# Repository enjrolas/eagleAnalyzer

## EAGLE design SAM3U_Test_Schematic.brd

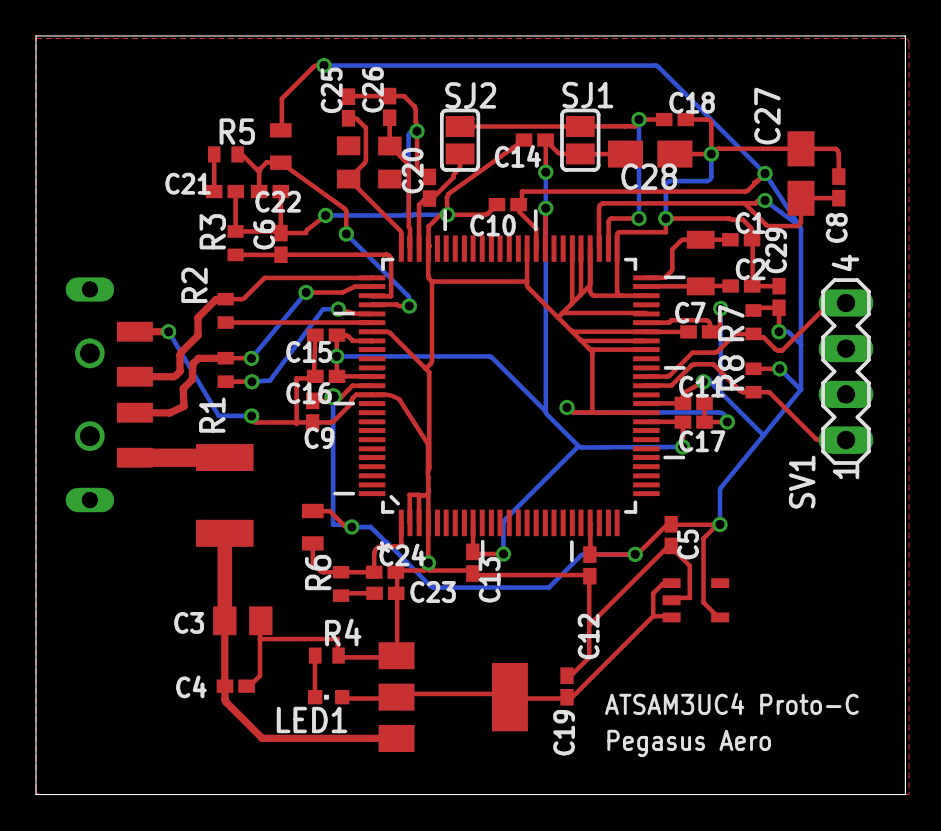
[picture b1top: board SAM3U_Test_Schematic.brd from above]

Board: 2 copper layers, 48.3 x 42.1 mm, 50 parts (0 on the bottom side), 24 nets.

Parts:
C1, C2, C25, C26: 20pF; C0402K
C3: 33uF; C0805K
C4, C7, C8, C9, C10, C11, C12, C13, C14, C15, C16, C17, C19, C20, C22, C24: 0.1uF; C0402K
C5: 10uF; C0402K
C6: 10pF; C0402K
C18, C21, C23: 4.7uF; C0402K
C27, C28: 10uF; A/3216-18R
C29: 10nF; C0402K
L1, L2: TDK_MLZ2012_INDUCTOR; TDK_MLZ_INDUCTOR_2012PACK
LED1: CHIPLED_0603
R1, R2: 39R; R0402
R3: 6.8K 1%; R0402
R4: 220R; R0402
R5, R6: 1R; R0402
R7, R8: 4.7K; R0402
SJ1, SJ2: SJ
SV1: MA04-1
U$1: USB_TYPE_A_KEYSTN; USB_TYPE_PLUG_KSTN_PACK
U$2: ATSAM3UC4-PA; QFP50P1600X1600X160-100N
U$3: 32678_KYOCERA; 32678_KYOCERA_PACK
U$4: MF-MSMF050-2; MF-MSMF050-PACK
U$5: NCP1117-55V; NCP1117-5-SOT
U$6: LP2985-33DBVR5-PIN; LP2985-33DBVR-SO
U$7: AVX_12MHZ_CRYSTAL_CX3225GB; AVX_12MHZ_CX3225GB_PACK

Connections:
+3V3: C5.1, C7.1, C8.1, C9.1, C10.1, C11.1, C12.1, C27.+, C29.1, L1.1, L2.1, R7.1, R8.1, U$2.22, U$2.36, U$2.45, U$2.53, U$2.60, U$2.88, U$6.5
+5V: C19.1, LED1.A, U$5.2, U$5.4, U$6.1, U$6.3
DFSDM: R1.2, U$2.80
DHSDM: R1.1, U$1.2, U$2.77
DHSDP: R2.1, U$1.3, U$2.76
GND: C1.2, C2.2, C3.2, C4.2, C5.2, C6.2, C7.2, C8.2, C9.2, C10.2, C11.2, C12.2, C13.2, C14.2, C15.2, C16.2, C17.2, C18.2, C19.2, C20.2, C21.2, C22.2, C23.2, C24.2, C25.2, C26.2, C27.-, C28.-, C29.2, R3.2, R4.2, U$1.4, U$2.2, U$2.3, U$2.4, U$2.35, U$2.42, U$2.43, U$2.44, U$2.46, U$2.48, U$2.51, U$2.54, U$2.55, U$2.56, U$2.61, U$2.72, U$2.82, U$2.89, U$5.1, U$6.2
unnamed: C2.1, U$2.49, U$3.2
unnamed: C1.1, U$2.50, U$3.1
unnamed: C26.1, U$2.74, U$7.3
unnamed: R2.2, U$2.81
unnamed: C3.1, C4.1, U$4.2, U$5.3
unnamed: LED1.C, R4.1
unnamed: C21.1, R5.1
unnamed: C23.1, R6.1
unnamed: C25.1, U$2.75, U$7.1
SCL0: R7.2, SV1.4, U$2.39
SDA0: R8.2, SV1.1, U$2.38
VBG: C6.1, R3.1, U$2.78
VBUS: U$1.1, U$4.1
VDDANA: C24.1, L2.2, R6.2, U$2.1
VDDCORE: C13.1, C14.1, C15.1, C16.1, C17.1, C28.+, SJ1.2, U$2.9, U$2.34, U$2.59, U$2.83, U$2.87
VDDOUT: C18.1, SJ1.1, SJ2.1, U$2.52
VDDPLL: C20.1, SJ2.2, U$2.73
VDDUTMI: C22.1, L1.2, R5.2, U$2.79

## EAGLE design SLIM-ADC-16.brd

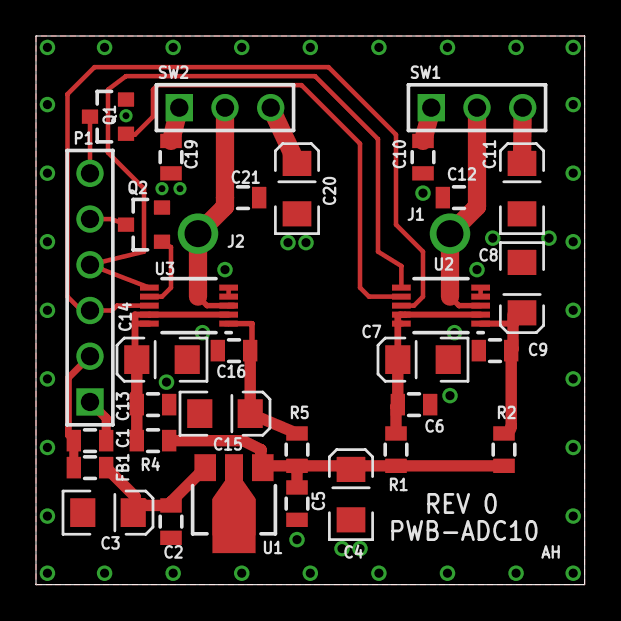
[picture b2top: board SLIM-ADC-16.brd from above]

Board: 2 copper layers, 30.5 x 30.5 mm, 34 parts (0 on the bottom side), 20 nets.

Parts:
C1, C2, C5, C6, C9, C10, C13, C16, C19: 0.1uF; 0805
C3, C4, C7, C8, C11, C14, C15, C20: 10uF/16V; EIA3216
C12, C21: 0.001uF; 0805
FB1: FERRITE0805; 0805
J1, J2: COAX; SLIM_COAX_PAD
P1: CONN-6PIN
Q1, Q2: MUN2211; SOT23
R1, R2, R4, R5: 10; 0805
SW1, SW2: SPDT-CONN; CONN-3PIN
U1: 78L05; SOT89
U2, U3: AD7685; MSOP10

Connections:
+5AD: C4.A, C5.1, R1.1, R2.2, R4.1, R5.2, U1.1
+10V: C1.1, FB1.1, P1.2
ACK: P1.5, Q2.C
CONVERT: P1.4, U2.6, U3.6
GND: C1.2, C2.2, C3.C, C4.C, C5.2, C6.2, C7.C, C8.C, C9.2, C10.2, C11.C, C12.2, C13.2, C14.C, C15.C, C16.2, C19.2, C20.C, C21.2, J1.P$2, J2.P$2, P1.1, Q1.E, Q2.E, U1.2, U1.4, U2.4, U2.5, U3.4, U3.5
unnamed: C8.A, C9.1, R2.1, U2.1
unnamed: C6.1, C7.A, R1.2, U2.2, U2.9, U2.10
unnamed: C12.1, J1.P$1, SW1.2, U2.3
unnamed: C10.1, SW1.1
unnamed: C11.A, SW1.3
unnamed: Q1.B, U2.7
unnamed: C2.1, C3.A, FB1.2, U1.3
unnamed: C15.A, C16.1, R5.1, U3.1
unnamed: C13.1, C14.A, R4.2, U3.2, U3.9, U3.10
unnamed: C21.1, J2.P$1, SW2.2, U3.3
unnamed: C19.1, SW2.1
unnamed: C20.A, SW2.3
unnamed: Q2.B, U3.7
SERCLOCK: P1.3, U2.8, U3.8
WAIT: P1.6, Q1.C

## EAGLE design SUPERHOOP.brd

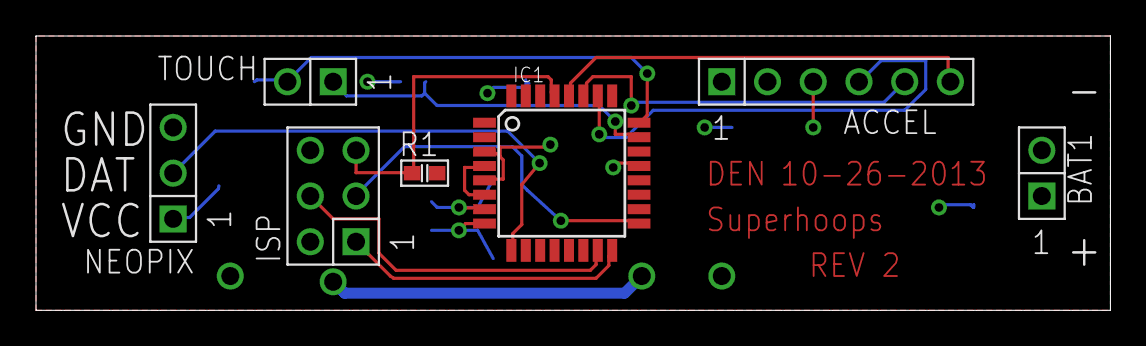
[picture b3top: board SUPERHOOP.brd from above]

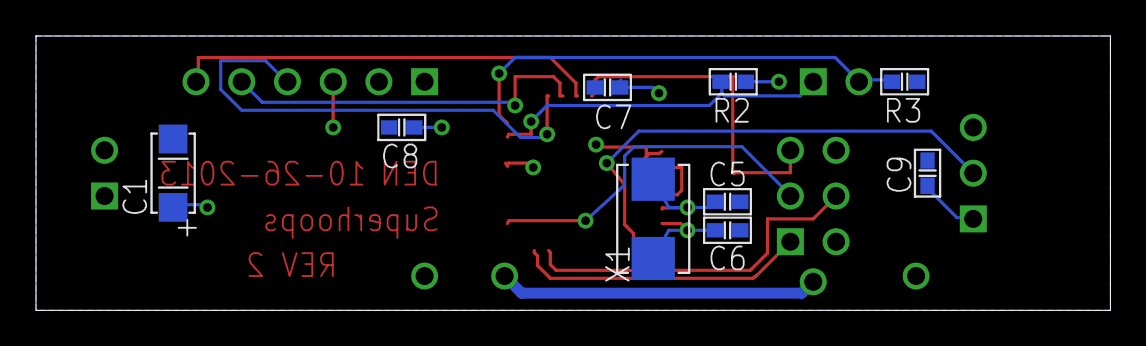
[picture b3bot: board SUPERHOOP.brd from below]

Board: 2 copper layers, 59.7 x 15.2 mm, 16 parts (9 on the bottom side), 14 nets.

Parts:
ACCEL: ADXL335_BBOARD_V2; HEADER_6X1_2.54
BAT1: Battery_lithium 3.7v (3x); HEADER_2X1_2.54
C1: 10uF; CAP_POL_1206
C5, C6: 22pF; SMD_0603
C7, C9: 100nF; SMD_0603
C8: 100nf; SMD_0603
IC1: MEGA8-AI; TQFP32-08
ISP: ISP-AVR_6P; HEADER_3X2_2.54
NEOPIX: LED_STRING_OUTPUT; HEADER_3X1_2.54
R1: 10k; SMD_0603
R2, R3: 470k; SMD_0603
TOUCH: TOUCH_INPUT; HEADER_2X1_2.54
X1: 16mhz; CRYSTAL_5.0X3.2

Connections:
DOUT: IC1.9, NEOPIX.2
GND: ACCEL.3, BAT1.2, C1.N, C5.P$1, C6.P$2, C7.P$2, C8.P$1, C9.P$2, IC1.3, IC1.5, IC1.21, ISP.6, NEOPIX.3, R3.P$1
MISO: IC1.16, ISP.1
MOSI: IC1.15, ISP.4
RST: IC1.29, ISP.5, R1.P$1
SCK: IC1.17, ISP.3
TOUCHA: IC1.23, R2.P$1, TOUCH.1
TOUCHB: IC1.24, R3.P$2, TOUCH.2
VCC: ACCEL.1, BAT1.1, C1.P, C7.P$1, C8.P$2, C9.P$1, IC1.4, IC1.6, IC1.18, IC1.20, ISP.2, NEOPIX.1, R1.P$2, R2.P$2
XOUT: ACCEL.6, IC1.28
XTAL1: C5.P$2, IC1.7, X1.P$1
XTAL2: C6.P$1, IC1.8, X1.P$2
YOUT: ACCEL.5, IC1.27
ZOUT: ACCEL.4, IC1.26

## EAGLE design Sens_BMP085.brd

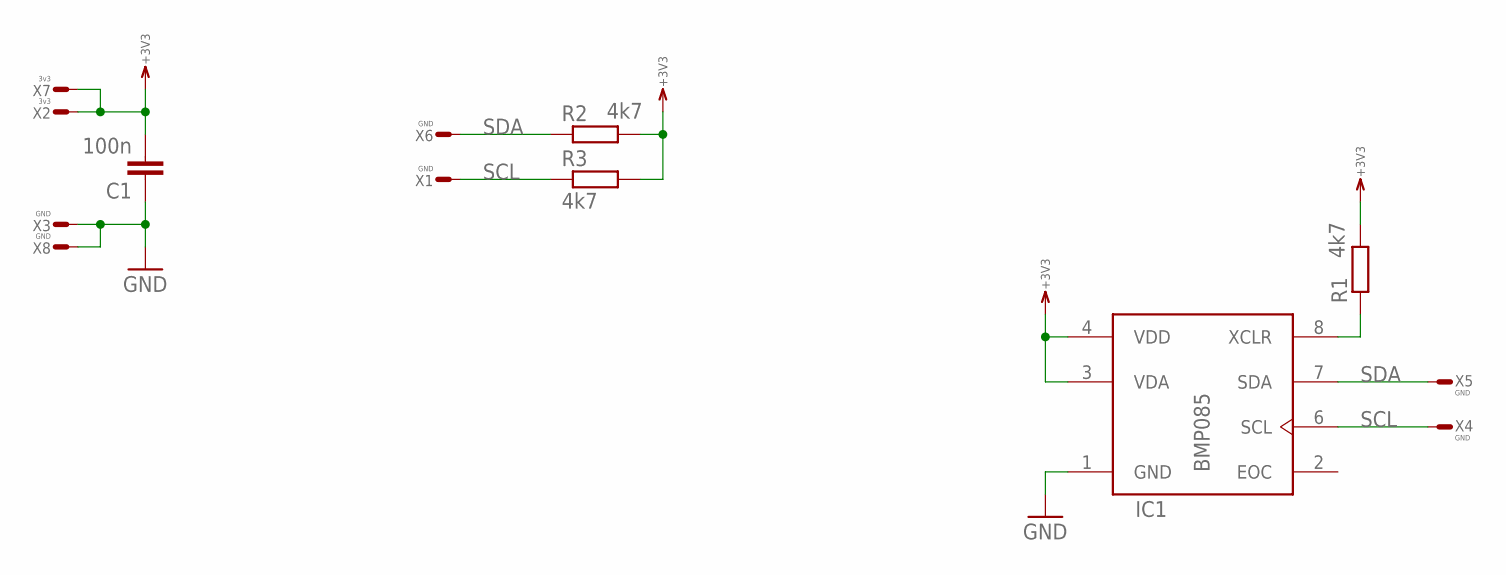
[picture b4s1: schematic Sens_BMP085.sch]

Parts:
C1: 100n; 0603
IC1: BMP085; LCC8
R1, R2, R3: 4k7; 0603
X1, X3, X4, X5, X6, X8: GND; T1.6/0.9
X2, X7: 3v3; T1.6/0.9

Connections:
+3V3: C1.2, IC1.3 (VDA), IC1.4 (VDD), R1.2, R2.2, R3.2, X2.1, X7.1
GND: C1.1, IC1.1 (GND), X3.1, X8.1
unnamed: IC1.8 (XCLR), R1.1
SCL: IC1.6 (SCL), R3.1, X1.1, X4.1
SDA: IC1.7 (SDA), R2.1, X5.1, X6.1

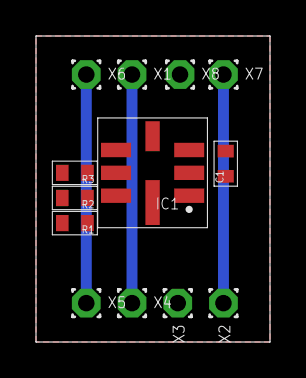
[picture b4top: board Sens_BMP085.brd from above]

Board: 2 copper layers, 13.0 x 17.0 mm, 13 parts (0 on the bottom side), 5 nets.

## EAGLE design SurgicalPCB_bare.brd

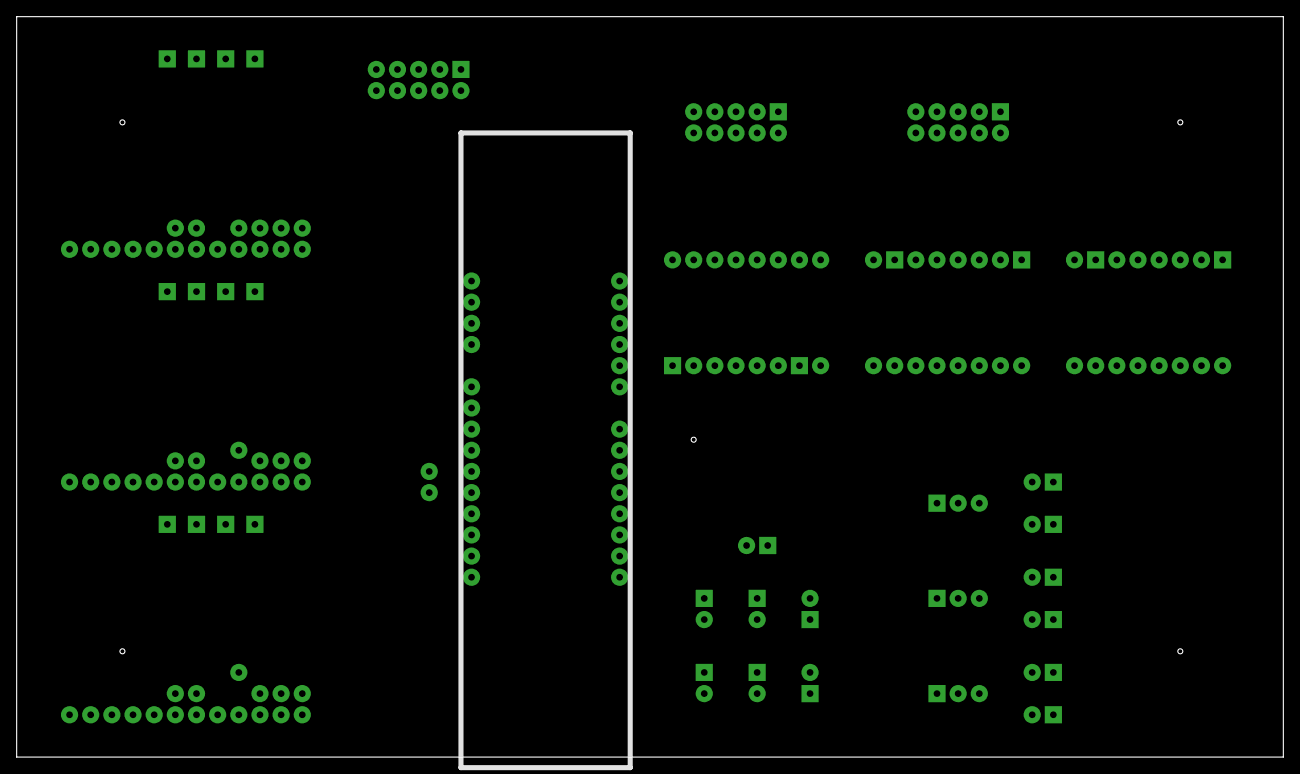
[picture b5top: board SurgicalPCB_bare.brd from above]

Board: 2 copper layers, 152.1 x 88.9 mm, 31 parts (0 on the bottom side), 60 nets, no tracks yet.

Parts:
6V, 10V: V_REG
EV: V_REG
E_STOP: RESISTOR
LED_GREEN: RESISTOR
LED_R: RESISTOR
LED_RES: RESISTOR
LED_RES_G: RESISTOR
POWERPLUG: RESISTOR
POWER_SWITCH: RESISTOR
RES6-1: RESISTOR
RES_6-2, RES_10-1, RES_10-2: RESISTOR
RES_EV-1, RES_EV-2: RESISTOR
U$1, U$2, U$3: A4955
U$4: BOARDUINOSTD; BOARDUINO
U$5, U$6, U$7: MC33926
U$8, U$9, U$10: 2_5_RIBBON
U$14, U$23, U$24, U$25, U$26: PROPE_HOLE

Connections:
6V_RAIL: 6V.VOUT, RES6-1.VIN, U$5.M_VIN, U$6.M_VIN
10V_RAIL: 10V.VOUT, RES_10-1.VIN, U$1.VMOT, U$2.VMOT, U$3.VMOT, U$4.VIN, U$7.M_VIN
24V_1: POWERPLUG.VOUT, POWER_SWITCH.VIN
24V_2: E_STOP.VIN, LED_RES.VIN, POWER_SWITCH.VOUT
24V_3: LED_R.VIN, LED_RES.VOUT
24V_4: 6V.VIN, 10V.VIN, EV.VIN, E_STOP.VOUT, LED_RES_G.VIN
24V_5: LED_GREEN.VIN, LED_RES_G.VOUT
GND: LED_GREEN.VOUT, LED_R.VOUT, POWERPLUG.VIN, RES_6-2.VOUT, RES_10-2.VOUT, RES_EV-2.VOUT, U$1.GND, U$1.GND_2, U$2.GND, U$2.GND_2, U$3.GND, U$3.GND_2, U$4.GND_3, U$5.GND, U$5.IN2, U$5.M_GND, U$6.GND, U$6.IN2, U$6.M_GND, U$7.GND, U$7.IN2, U$7.M_GND, U$9.2
LOGIC_HIGH_RAIL: U$1.!RST, U$1.VDD, U$2.!RST, U$2.VDD, U$3.!RST, U$3.VDD, U$4.5V_2, U$5.IN1, U$5.VDD, U$6.IN1, U$6.VDD, U$7.IN1, U$7.VDD, U$8.1
unnamed: U$3.STEP, U$4.12
unnamed: U$1.!SLP, U$2.!SLP, U$3.!SLP, U$4.D8
unnamed: U$1.DIT, U$2.DIT, U$3.DIT, U$4.D9
unnamed: U$1.STEP, U$4.10
unnamed: U$2.STEP, U$4.11
unnamed: U$7.FB, U$14.P$1
unnamed: U$6.FB, U$23.P$1
unnamed: U$5.JP_PWM/D2, U$5.PWN/D2
unnamed: U$5.JP_PWM/D1, U$5.PWM/D1
unnamed: U$5.JP_SLEW, U$5.SLEW
unnamed: U$5.FB, U$24.P$1
unnamed: U$4.D3, U$25.P$1
unnamed: U$6.JP_PWM/D2, U$6.PWN/D2
unnamed: U$6.JP_PWM/D1, U$6.PWM/D1
unnamed: U$6.JP_SLEW, U$6.SLEW
unnamed: U$4.D2, U$26.P$1
unnamed: U$7.JP_PWM/D2, U$7.PWN/D2
unnamed: U$7.JP_PWM/D1, U$7.PWM/D1
unnamed: U$7.JP_SLEW, U$7.SLEW
unnamed: U$4.D7, U$5.INV, U$6.INV, U$7.INV
unnamed: U$5.M_OUT2, U$8.10
unnamed: U$4.D6, U$5.EN
unnamed: U$4.D5, U$6.EN
unnamed: U$4.D4, U$7.EN
unnamed: U$5.M_OUT1, U$8.8
unnamed: U$6.M_OUT2, U$8.3
unnamed: U$6.M_OUT1, U$8.5
unnamed: U$7.M_OUT2, U$8.7
unnamed: U$7.M_OUT1, U$8.9
unnamed: U$4.A2, U$8.6
unnamed: U$4.A1, U$8.4
unnamed: U$4.A0, U$8.2
unnamed: U$3.2B, U$10.2
unnamed: U$3.2A, U$10.4
unnamed: U$3.1A, U$10.6
unnamed: U$3.1B, U$10.8
unnamed: U$4.A5, U$10.10
unnamed: U$2.1B, U$10.1
unnamed: U$2.1A, U$10.3
unnamed: U$2.2A, U$10.5
unnamed: U$2.2B, U$10.7
unnamed: U$4.A4, U$10.9
unnamed: U$1.2B, U$9.9
unnamed: U$1.2A, U$9.7
unnamed: U$1.1A, U$9.5
unnamed: U$1.1B, U$9.3
unnamed: U$4.A3, U$9.1
unnamed: 10V.ADJ, RES_10-1.VOUT, RES_10-2.VIN
unnamed: 6V.ADJ, RES6-1.VOUT, RES_6-2.VIN
unnamed: EV.VOUT, RES_EV-1.VIN
unnamed: EV.ADJ, RES_EV-1.VOUT, RES_EV-2.VIN

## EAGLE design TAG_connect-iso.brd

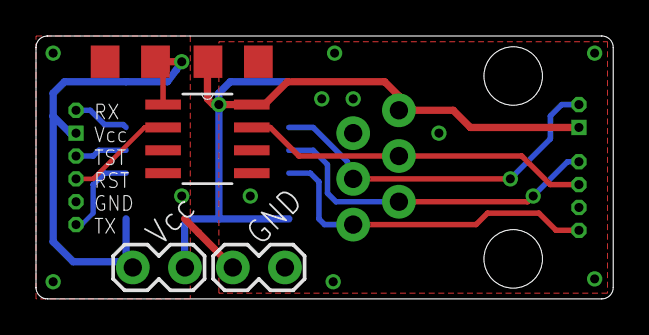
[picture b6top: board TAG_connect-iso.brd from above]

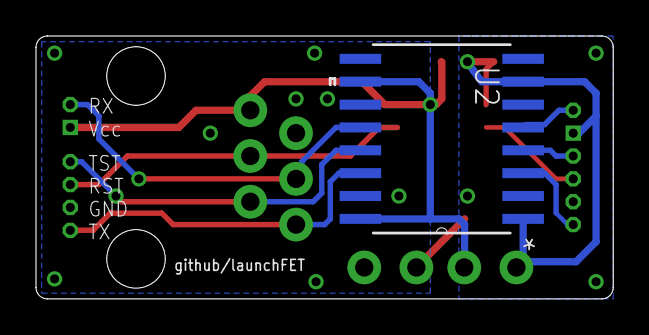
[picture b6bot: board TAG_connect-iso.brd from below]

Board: 2 copper layers, 32.1 x 14.6 mm, 9 parts (2 on the bottom side), 12 nets.

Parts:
C1, C2: C1206
J2: RJ11-6PTH; RJ11-6
JP1, JP2: 1X02_LOCK
U2: ISO7231C_DW_16; DW16
U$2: ISO1540; D8
U$4: 6-PIN-ICSPEASY-MSP; EASYMSP-6PIN
U$5: 6-PIN-ICSPSAFE-MSP; SAFEMSP-6PIN

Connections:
GND_FET: C2.2, JP2.2, U2.2, U2.8, U$2.4, U$4.GND
GND_TARGET: C1.2, J2.5, JP2.1, U2.9, U2.15, U$2.5, U$5.GND
RESET_FET: U$2.2, U$4.RST
RESET_TARGET: J2.4, U$2.7, U$5.RST
RX_FET: U2.5, U$4.RX
RX_TARGET: J2.3, U2.12, U$5.RX
TEST_FET: U2.4, U$4.TST
TEST_TARGET: J2.2, U2.13, U$5.TST
TX_FET: U2.3, U$4.TX
TX_TARGET: J2.1, U2.14, U$5.TX
VCC_FET: C2.1, JP1.1, U2.1, U2.7, U$2.1, U$4.VCC
VCC_TARGET: C1.1, J2.6, JP1.2, U2.10, U2.16, U$2.8, U$5.VCC

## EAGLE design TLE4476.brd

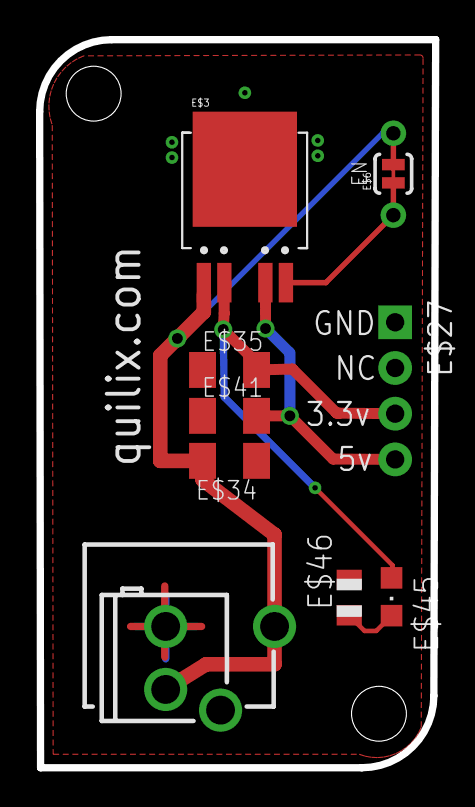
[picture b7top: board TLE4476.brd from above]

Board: 2 copper layers, 22.0 x 40.5 mm, 10 parts (0 on the bottom side), 6 nets.

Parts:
E$3: DPAK-5
E$6: SJ_2S-TRACE
E$11, E$12: STAND-OFF-TIGHT
E$27: 1X04_NO_SILK
E$34, E$35, E$41: C1206K
E$45: CHIPLED_0805
E$46: R0805

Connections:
3.3V: E$3.VIN, E$27.3, E$35.2, E$45.A
5V: E$3.VOUT, E$27.4, E$41.2
EN: E$3.ADJ, E$6.1
GND: E$3.GND, E$27.1, E$34.1, E$35.1, E$41.1, E$46.2
S$4: E$45.C, E$46.1
VIN: E$3.EN, E$6.2, E$34.2

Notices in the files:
parts and their libraries:
SparkFun-Connectors: Licensing: CC v3.0 Share-Alike You are welcome to use this library for commercial purposes.
